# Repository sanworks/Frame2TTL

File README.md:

# Frame2TTL
Hardware and software to capture discrete pixel intensity transitions from a small patch of an LCD screen. Transitions are reported as TTL pulses. This device is used to provide precise measurements of frame onset time in visual stimulus presentation

The bill of materials and other documentation is available at:
https://sites.google.com/site/frame2ttl

Frame2TTL is a product of Sanworks LLC, licensed under GPL v3.0 (see included license)
http://sanworks.io

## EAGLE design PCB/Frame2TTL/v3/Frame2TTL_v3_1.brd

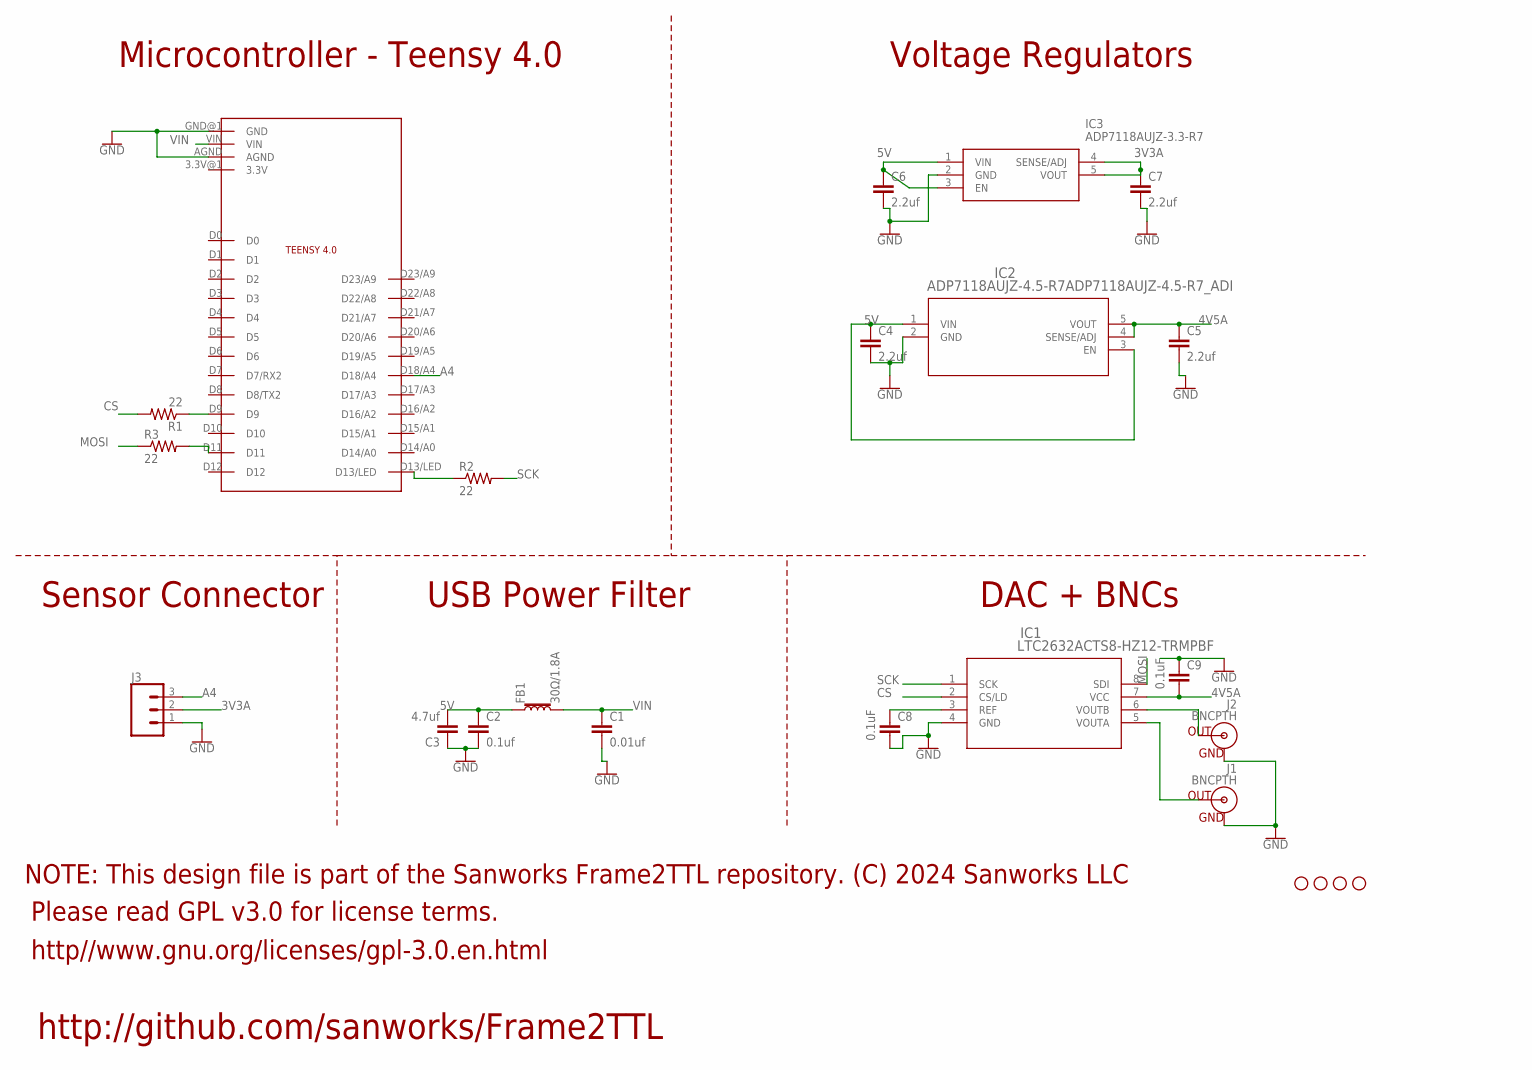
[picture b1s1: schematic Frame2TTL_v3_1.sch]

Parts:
C1: 0.01uf; 0805
C2: 0.1uf; 0805
C3: 4.7uf; 1206@2
C4, C5, C6, C7: 2.2uf; 0805
C8, C9: 0.1uF; 0805
FB1: 30Ω/1.8A; 0603
H1, H2, H3, H4: STAND-OFF
IC1: LTC2632ACTS8-HZ12-TRMPBF; TSOT-23-8_1P625X2P9_ADI
IC2: ADP7118AUJZ-4.5-R7ADP7118AUJZ-4.5-R7_ADI; ADP7118AUJZ-4.5-R7_ADI
IC3: ADP7118AUJZ-3.3-R7; SOT95P280X100-5N
J1, J2: BNCPTH; BNC
J3: CONN_03LOCK; 1X03_LOCK
MC1: TEENSY4.0_SIMPLE_NO_VUSB
R1, R2, R3: 22; R0805

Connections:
3V3A: C7.1, IC3.4 (SENSE/ADJ), IC3.5 (VOUT), J3.2
4V5A: C5.1, C9.2, IC1.7 (VCC), IC2.4 (SENSE/ADJ), IC2.5 (VOUT)
5V: C2.1, C3.2, C4.1, C6.1, FB1.1, IC2.1 (VIN), IC2.3 (EN), IC3.1 (VIN), IC3.3 (EN)
A4: J3.3, MC1.D18/A4
CS: IC1.2 (CS/LD), R1.2
GND: C1.2, C2.2, C3.1, C4.2, C5.2, C6.2, C7.2, C8.2, C9.1, IC1.4 (GND), IC2.2 (GND), IC3.2 (GND), J1.GND, J2.GND, J3.1, MC1.AGND, MC1.GND@1 (GND)
MOSI: IC1.8 (SDI), R3.1
unnamed: MC1.D11, R3.2
unnamed: MC1.D9, R1.1
unnamed: MC1.D13/LED, R2.1
unnamed: IC1.5 (VOUTA), J1.S (OUT)
unnamed: IC1.6 (VOUTB), J2.S (OUT)
unnamed: C8.1, IC1.3 (REF)
SCK: IC1.1 (SCK), R2.2
VIN: C1.1, FB1.2, MC1.VIN

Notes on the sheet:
Please read GPL v3.0 for license terms.
NOTE: This design file is part of the Sanworks Frame2TTL repository. (C) 2024 Sanworks LLC
http://github.com/sanworks/Frame2TTL
http//www.gnu.org/licenses/gpl-3.0.en.html
Microcontroller - Teensy 4.0
Voltage Regulators
USB Power Filter
Sensor Connector
DAC + BNCs

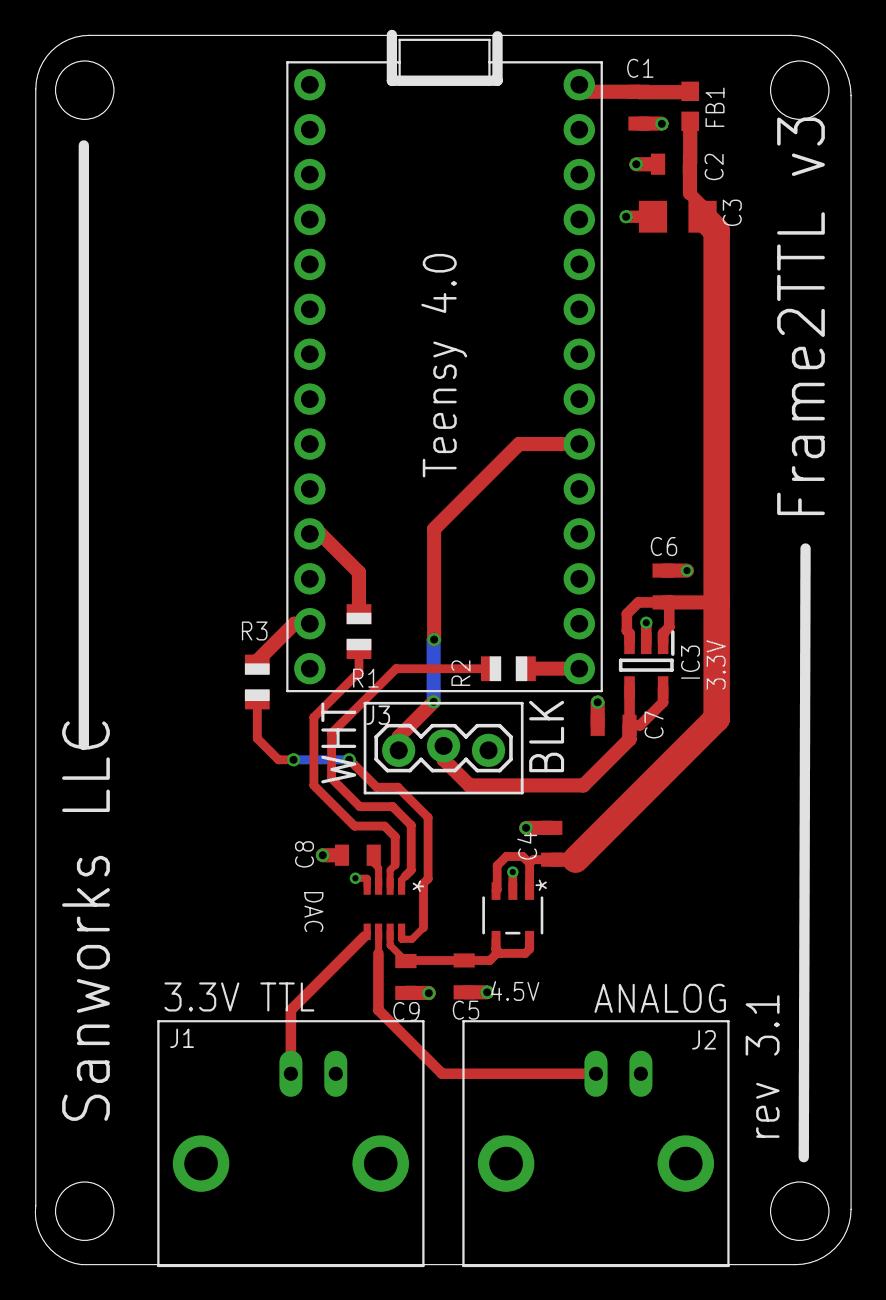
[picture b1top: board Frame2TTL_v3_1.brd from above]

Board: 2 copper layers, 46.1 x 69.5 mm, 24 parts (0 on the bottom side), 15 nets.

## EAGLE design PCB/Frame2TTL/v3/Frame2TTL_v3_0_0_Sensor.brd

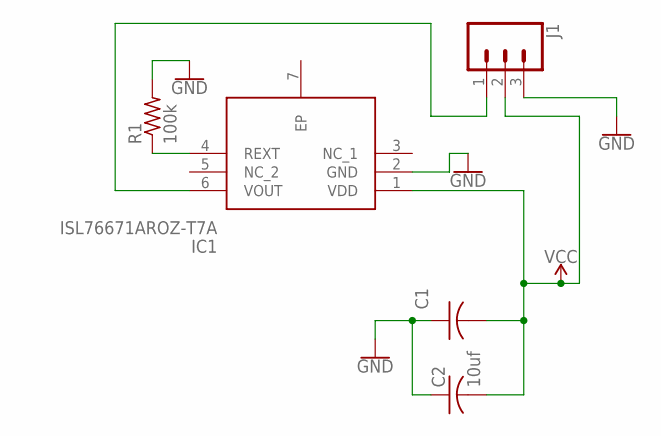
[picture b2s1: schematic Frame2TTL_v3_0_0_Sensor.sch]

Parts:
C1: 0.1uf; C0603K
C2: 10uf; C0805K
IC1: ISL76671AROZ-T7A; SON65P210X200X80-7N
J1: CONN_03LOCK; 1X03_LOCK
R1: 100k; R0805

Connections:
GND: C1.1, C2.1, IC1.2 (GND), J1.3, R1.2
unnamed: IC1.6 (VOUT), J1.1
unnamed: IC1.4 (REXT), R1.1
VCC: C1.2, C2.2, IC1.1 (VDD), J1.2

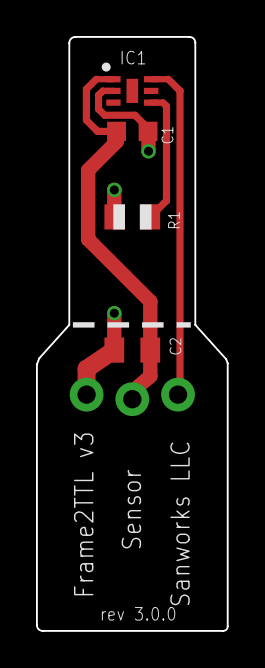
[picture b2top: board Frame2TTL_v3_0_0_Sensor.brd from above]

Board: 2 copper layers, 10.6 x 33.0 mm, 5 parts (1 on the bottom side), 4 nets.

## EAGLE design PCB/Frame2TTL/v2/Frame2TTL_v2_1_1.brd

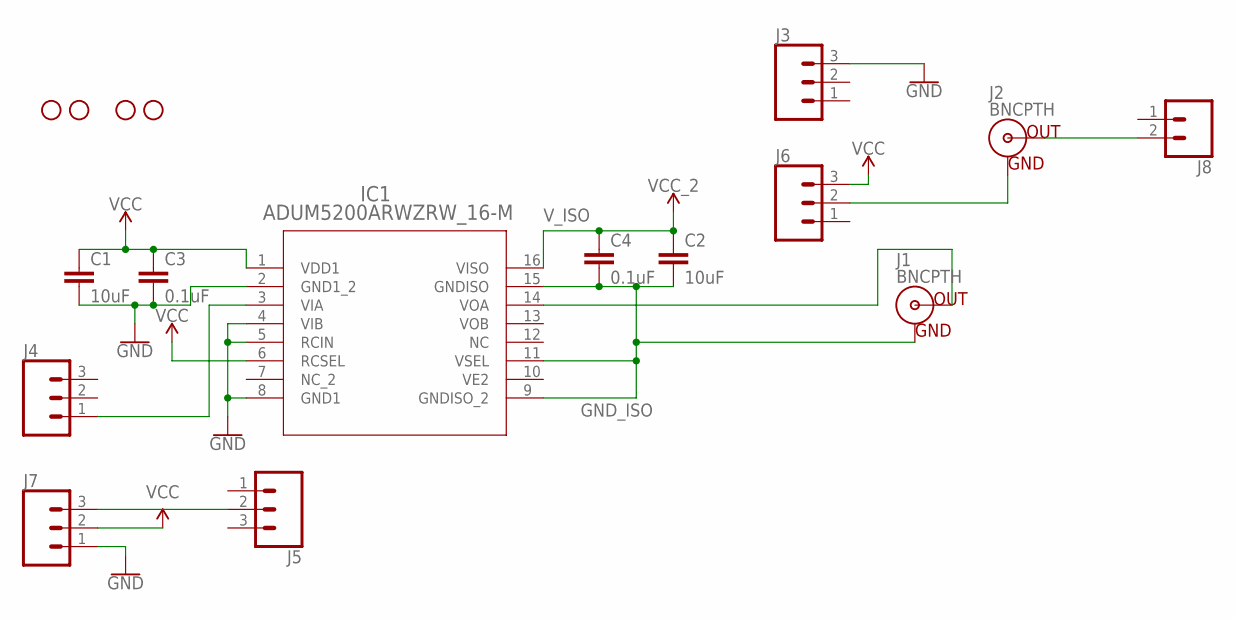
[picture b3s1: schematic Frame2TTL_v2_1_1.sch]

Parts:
C1, C2: 10uF; 1206
C3, C4: 0.1uF; 0805
H1, H2, H3, H4: STAND-OFF
IC1: ADUM5200ARWZRW_16-M; RW_16-M
J1, J2: BNCPTH; BNC
J3, J4, J5, J6, J7: CONN_03LOCK; 1X03_LOCK
J8: CONN_02; 1X02

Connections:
AGND: J2.GND, J6.2
GND: C1.2, C3.2, IC1.2 (GND1_2), IC1.4 (VIB), IC1.5 (RCIN), IC1.8 (GND1), J3.3, J7.1
GND_ISO: C2.2, C4.2, IC1.9 (GNDISO_2), IC1.11 (VSEL), IC1.15 (GNDISO), J1.GND
unnamed: J2.S (OUT), J8.2
unnamed: IC1.3 (VIA), J4.1
unnamed: J5.2, J7.3
unnamed: IC1.14 (VOA), J1.S (OUT)
VCC: C1.1, C3.1, IC1.1 (VDD1), IC1.6 (RCSEL), J6.3, J7.2
V_ISO: C2.1, C4.1, IC1.16 (VISO)

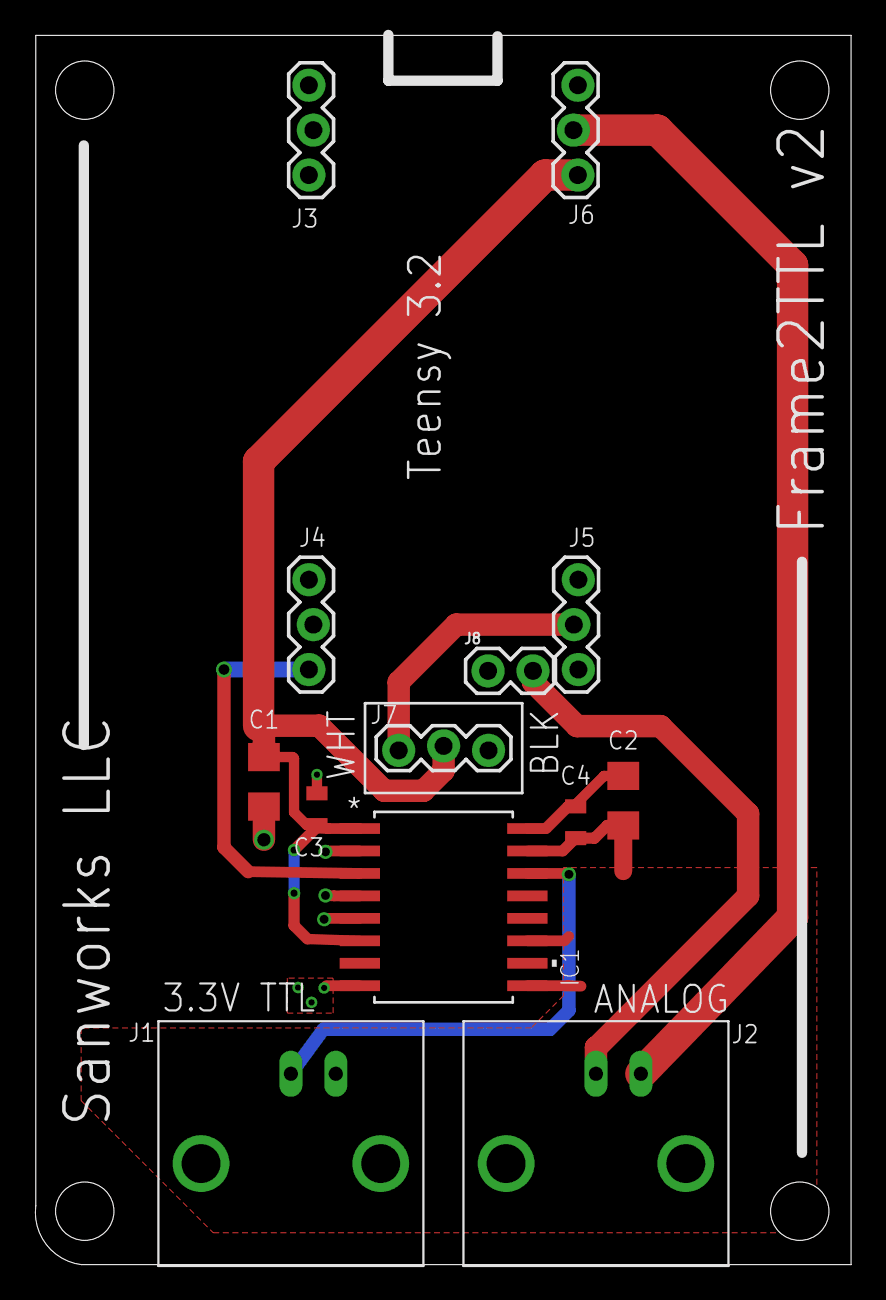
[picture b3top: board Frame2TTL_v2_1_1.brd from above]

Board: 2 copper layers, 46.1 x 69.5 mm, 17 parts (0 on the bottom side), 9 nets.

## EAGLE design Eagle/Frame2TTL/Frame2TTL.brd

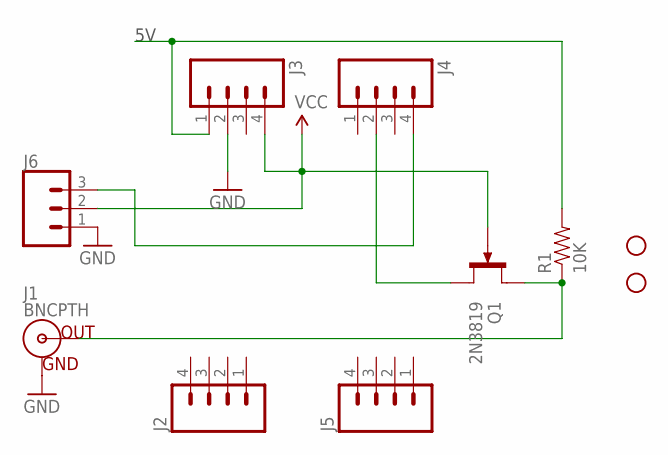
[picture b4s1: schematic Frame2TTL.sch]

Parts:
H1, H2: STAND-OFFTIGHT; STAND-OFF-TIGHT
J1: BNCPTH; BNC
J2, J3, J4, J5: M04PTH; 1X04
J6: CONN_03SCREW_LOCK; SCREWTERMINAL-3.5MM-3_LOCK.007S
Q1: 2N3819; TO92F
R1: 10K; AXIAL-0.3

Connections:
5V: J3.1, R1.P$2 (2)
GND: J1.GND, J3.2, J6.1
unnamed: J4.4, J6.3
unnamed: J4.2, Q1.S
unnamed: J1.S (OUT), Q1.D, R1.P$1 (1)
VCC: J3.4, J6.2, Q1.G

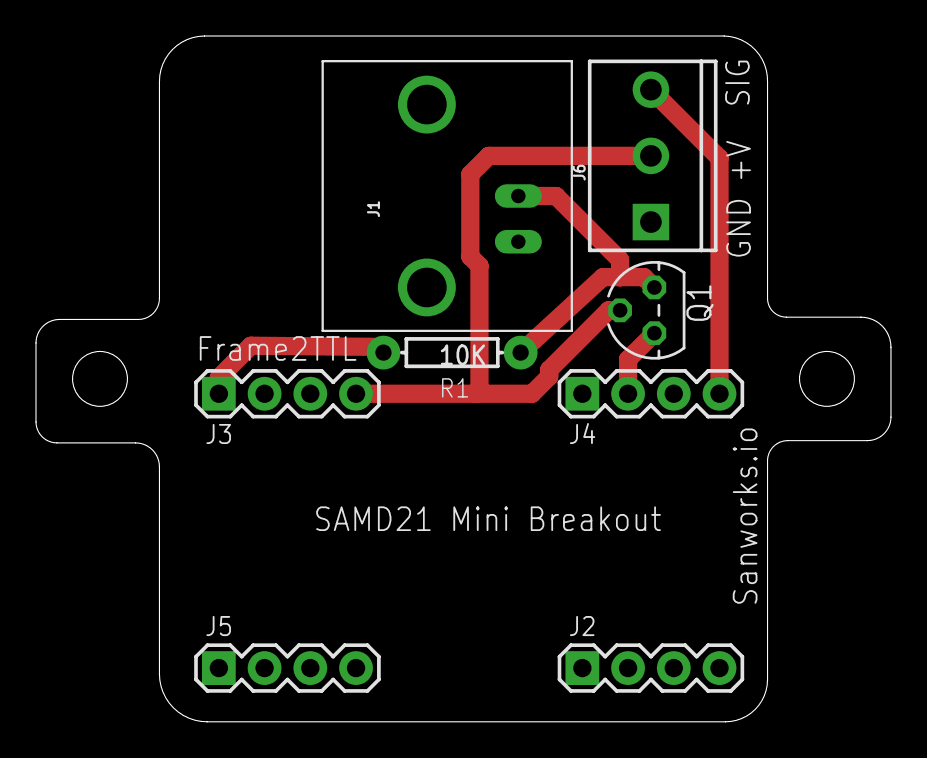
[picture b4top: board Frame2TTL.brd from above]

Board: 2 copper layers, 47.5 x 38.1 mm, 10 parts (0 on the bottom side), 6 nets.

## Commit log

2017-03-26 -Initial Commit
2017-04-17 -Added 3D printable shield to protect PCB bottom from conductors -Added experimental firmware containing an optional sliding window average filter. Updated MATLAB object to set sliding window #sample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
2018-04-19 -Set default thresholds in MATLAB class to match firmware defaults -Removed signal-filtering version of firmware
2019-11-01 stl files added for ease of printing
    The STL files were not available, so the Sketchup Files were individually exported (exports erred with random boxes added, so they were cleaned up), and STL's were combined in a good printing orienta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
2020-01-03 Updated Frame2TTL class to initialize threshold variables with default thresholds
2021-10-18 -Added Frame2TTL v2: CAD, Firmware, MATLAB+Python
2022-01-05 -Updated default dark --> light threshold for Frame2TTL v2. Note: on Ipad screens, the sync patch should be rendered at 50% intensity to avoid saturating the sensor.
2022-12-01 -Updated usage comments in MATLAB class
2023-08-01 -Added firmware and MATLAB software for hardware v3
2023-08-11 -Added code and CAD for Frame2TTL v3.0.0
2023-09-13 -Added Python support for Frame2TTL v3 -Updated firmware to compile for v2 or v3 -Reorganized repository
2023-09-13 -Corrections to Readme in root folder
2023-09-13 -Removed an experimental 3D print file -Renamed 3D print and laser cutting files for clarity
2023-09-13 -MATLAB: Fixed a bug that doubled the timescale of the display
2023-09-13 -Firmware: Fixed a pin assignment bug when compiling for hardware v2
2023-09-15 -Frame2TTL v1 Firmware: Added soft reset 50 seconds after PC boot. This circumvents an issue affecting hardware v1, where the USB serial interface is non-reponsive after PC reboot on Win10 -Removed r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
2023-09-15 -Frame2TTL v1 firmware: Disabled soft reset timer if serial port is opened
2023-11-03 -v3 3D-printed parts: Added a design version where the sensor can be removed from the side arm after assembly, by using a friction fit instead of a locking tab.
2024-02-26 -PCB: Added circuit board revision 3.1, optimizing fit of BNC connector mounts -3D printed parts: r1_1 with optimized press fits -Updated PCB version naming convention
2024-03-19 -Incremented firmware to v4 -Added DetectMode, a parameter to set the frame detection algorithm. In DetectMode 0, the threshold is of a moving average of sample-wise change in luminance. In DetectMod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
2024-03-19 -Reversed order of Detect-Mode values. 0 = luminance threshold, 1 (default) = sliding window average of sample-wise luminance change
2024-03-19 -Added a safety margin to DetectMode 0. Thresholds are initially inactive, and become active when measured light exceeds threshold by a fixed margin.
2024-03-19 -Firmware: Fixed bug where threshold is active on startup
2024-03-19 -Added MATLAB firmware loading tool and firmware binaries -Added warning if future firmware detected by MATLAB or Python software
2024-03-19 -Fixed bug where setting DetectMode to the current value would overwrite thresholds in MATLAB and Python classes.
2024-03-19 -MATLAB: Added reference to new firmware load tool in the error message
2024-03-19 -MATLAB: Updated comments
2024-03-19 -MATLAB: Restricted DetectMode 0 on hardware v2
2024-03-19 -MATLAB: In DetectMode 0, setting threshold will update GUI threshold lines even during streaming.
2024-03-19 -Added gitignore
2024-03-19 -Python: Restricted Detect Mode 0 on Frame2TTL v2
2024-03-22 -Improved comments, added warning re: cable EMF

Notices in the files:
parts and their libraries:
SparkFun-Connectors: Licensing: Creative Commons ShareAlike 4.0 International - https://creativecommons.org/licenses/by-sa/4.0
COPYRIGHT: Copyright (C) 2022 Ultra Librarian. All rights reserved.
COPYRIGHT: Copyright (C) 2023 Ultra Librarian. All rights reserved.
